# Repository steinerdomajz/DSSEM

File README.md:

# System for Environmental Monitoring in Protected Areas
**Master's Thesis Project** | Brno University of Technology (FEKT VUT)

This repository contains a demonstration of my final thesis project: an autonomous IoT system designed for long-term monitoring of acoustic and light pollution in sensitive environments.

Presentation available: DSSEM_presentation.pdf

**Key Features**:
- **Autonomous Operation**: Powered by a solar energy harvesting system.
- **Low-Power Design**: Optimized for long-term deployment in remote areas with minimal maintenance.
- **Connectivity**: Real-time data transmission via NB-IoT.
- **Sensor Precision**: Integrated high-sensitivity sensors for measuring environmental noise and light levels.

**Tech Stack**:
- **Electronics**: Custom PCB designed in KiCad.
- **Firmware**: Developed for MCU to handle sensor data and communication protocols.
- **Mechanical Design**: Protective environmental casing designed in SolidWorks.

--- **Hardware Design & Implementation:** ---

--- **Firmware:** ---

--- **Mechanical Design:** ---

--- **Implementation:** ---

Node-RED Flowchart:

InfluxDB Visualisation:

User Configuration Site (Web Serial API):

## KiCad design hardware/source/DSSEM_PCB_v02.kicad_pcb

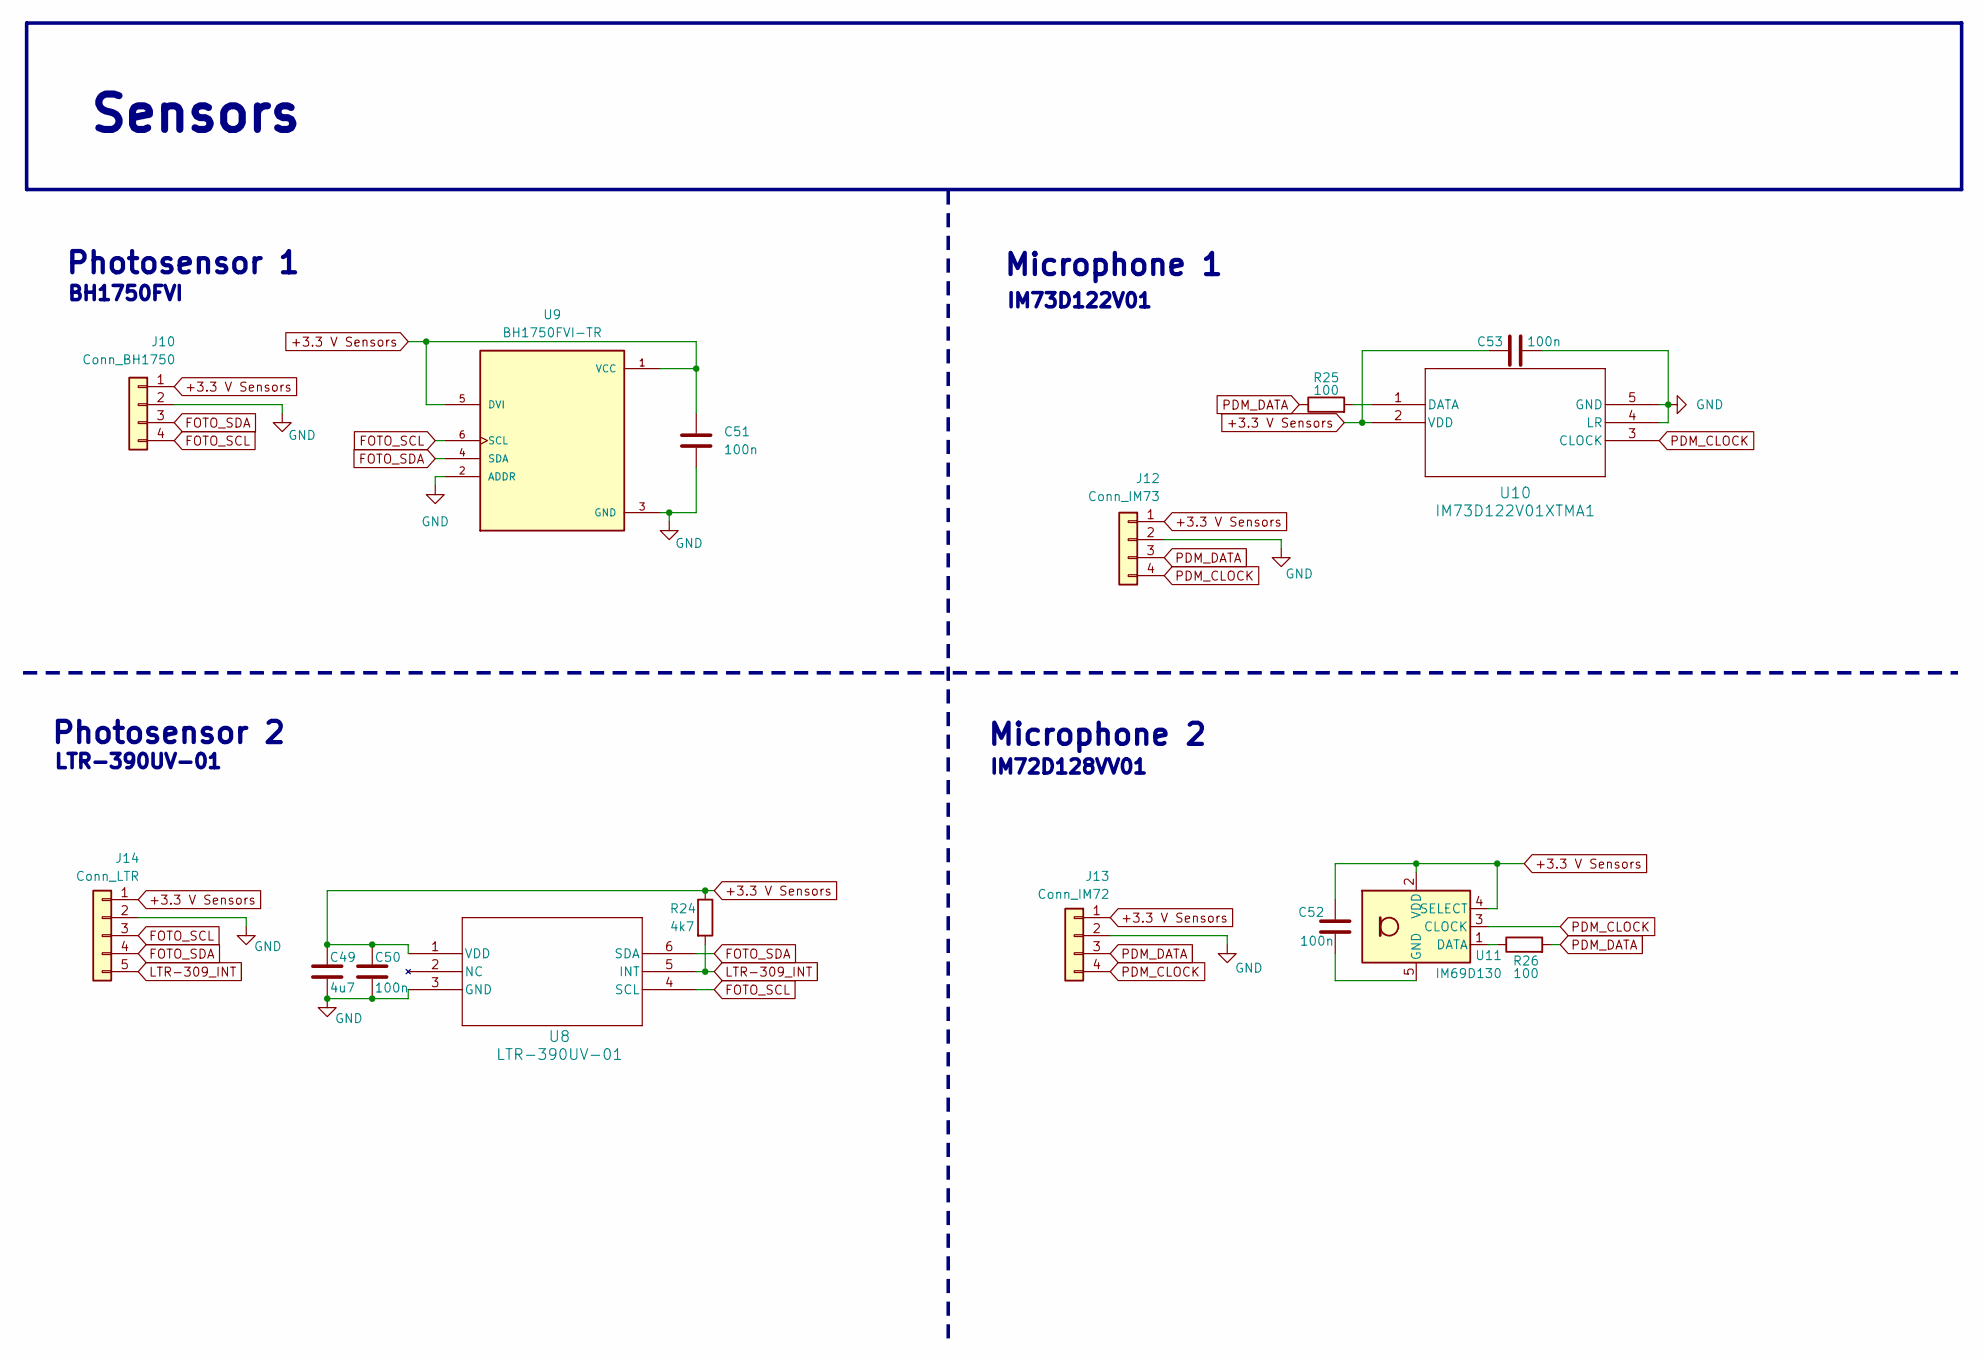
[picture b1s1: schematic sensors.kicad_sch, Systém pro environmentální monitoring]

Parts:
C49: 4u7; C_0603_1608Metric_Pad1.08x0.95mm_HandSolder
C50, C51, C52, C53: 100n; C_0603_1608Metric_Pad1.08x0.95mm_HandSolder
J10: Conn_BH1750; JST_GH_SM04B-GHS-TB_1x04-1MP_P1.25mm_Horizontal
J12: Conn_IM73; JST_GH_SM04B-GHS-TB_1x04-1MP_P1.25mm_Horizontal
J13: Conn_IM72; JST_GH_SM04B-GHS-TB_1x04-1MP_P1.25mm_Horizontal
J14: Conn_LTR; JST_GH_SM05B-GHS-TB_1x05-1MP_P1.25mm_Horizontal
R24: 4k7; R_0603_1608Metric_Pad0.98x0.95mm_HandSolder
R25, R26: 100; R_0603_1608Metric_Pad0.98x0.95mm_HandSolder
U8: LTR-390UV-01; SMD6_LTR-390UV-01_LTO
U9: BH1750FVI-TR; XDCR_BH1750FVI-TR; PARTREV D
U10: IM73D122V01XTMA1; Infineon_PG-LLGA-5-2
U11: IM69D130; Infineon_PG-LLGA-5-1

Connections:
+3.3 V Sensors: C49.1, C50.1, C51.1, C52.1, C53.1, J10.1, J12.1, J13.1, J14.1, R24.1, U8.1 (VDD), U9.1 (VCC), U9.5 (DVI), U10.2 (VDD), U11.2 (VDD), U11.4 (SELECT); also elsewhere on the board
FOTO_SCL: J10.4, J14.3, U8.4 (SCL), U9.6 (SCL); also elsewhere on the board
FOTO_SDA: J10.3, J14.4, U8.6 (SDA), U9.4 (SDA); also elsewhere on the board
GND: C49.2, C50.2, C51.2, C53.2, J10.2, J12.2, J13.2, J14.2, U8.3 (GND), U9.2 (ADDR), U9.3 (GND), U10.4 (LR), U10.5 (GND); also elsewhere on the board
LTR-309_INT: J14.5, R24.2, U8.5 (INT); also elsewhere on the board
unnamed: R25.2, U10.1 (DATA)
unnamed: R26.1, U11.1 (DATA)
unnamed: C52.2, U11.5 (GND)
PDM_CLOCK: J12.4, J13.4, U10.3 (CLOCK), U11.3 (CLOCK); also elsewhere on the board
PDM_DATA: J12.3, J13.3, R25.1, R26.2; also elsewhere on the board

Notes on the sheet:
Microphone 2
BH1750FVI
Photosensor 1
LTR-390UV-01
IM73D122V01
IM72D128VV01
Photosensor 2
Sensors
Microphone 1

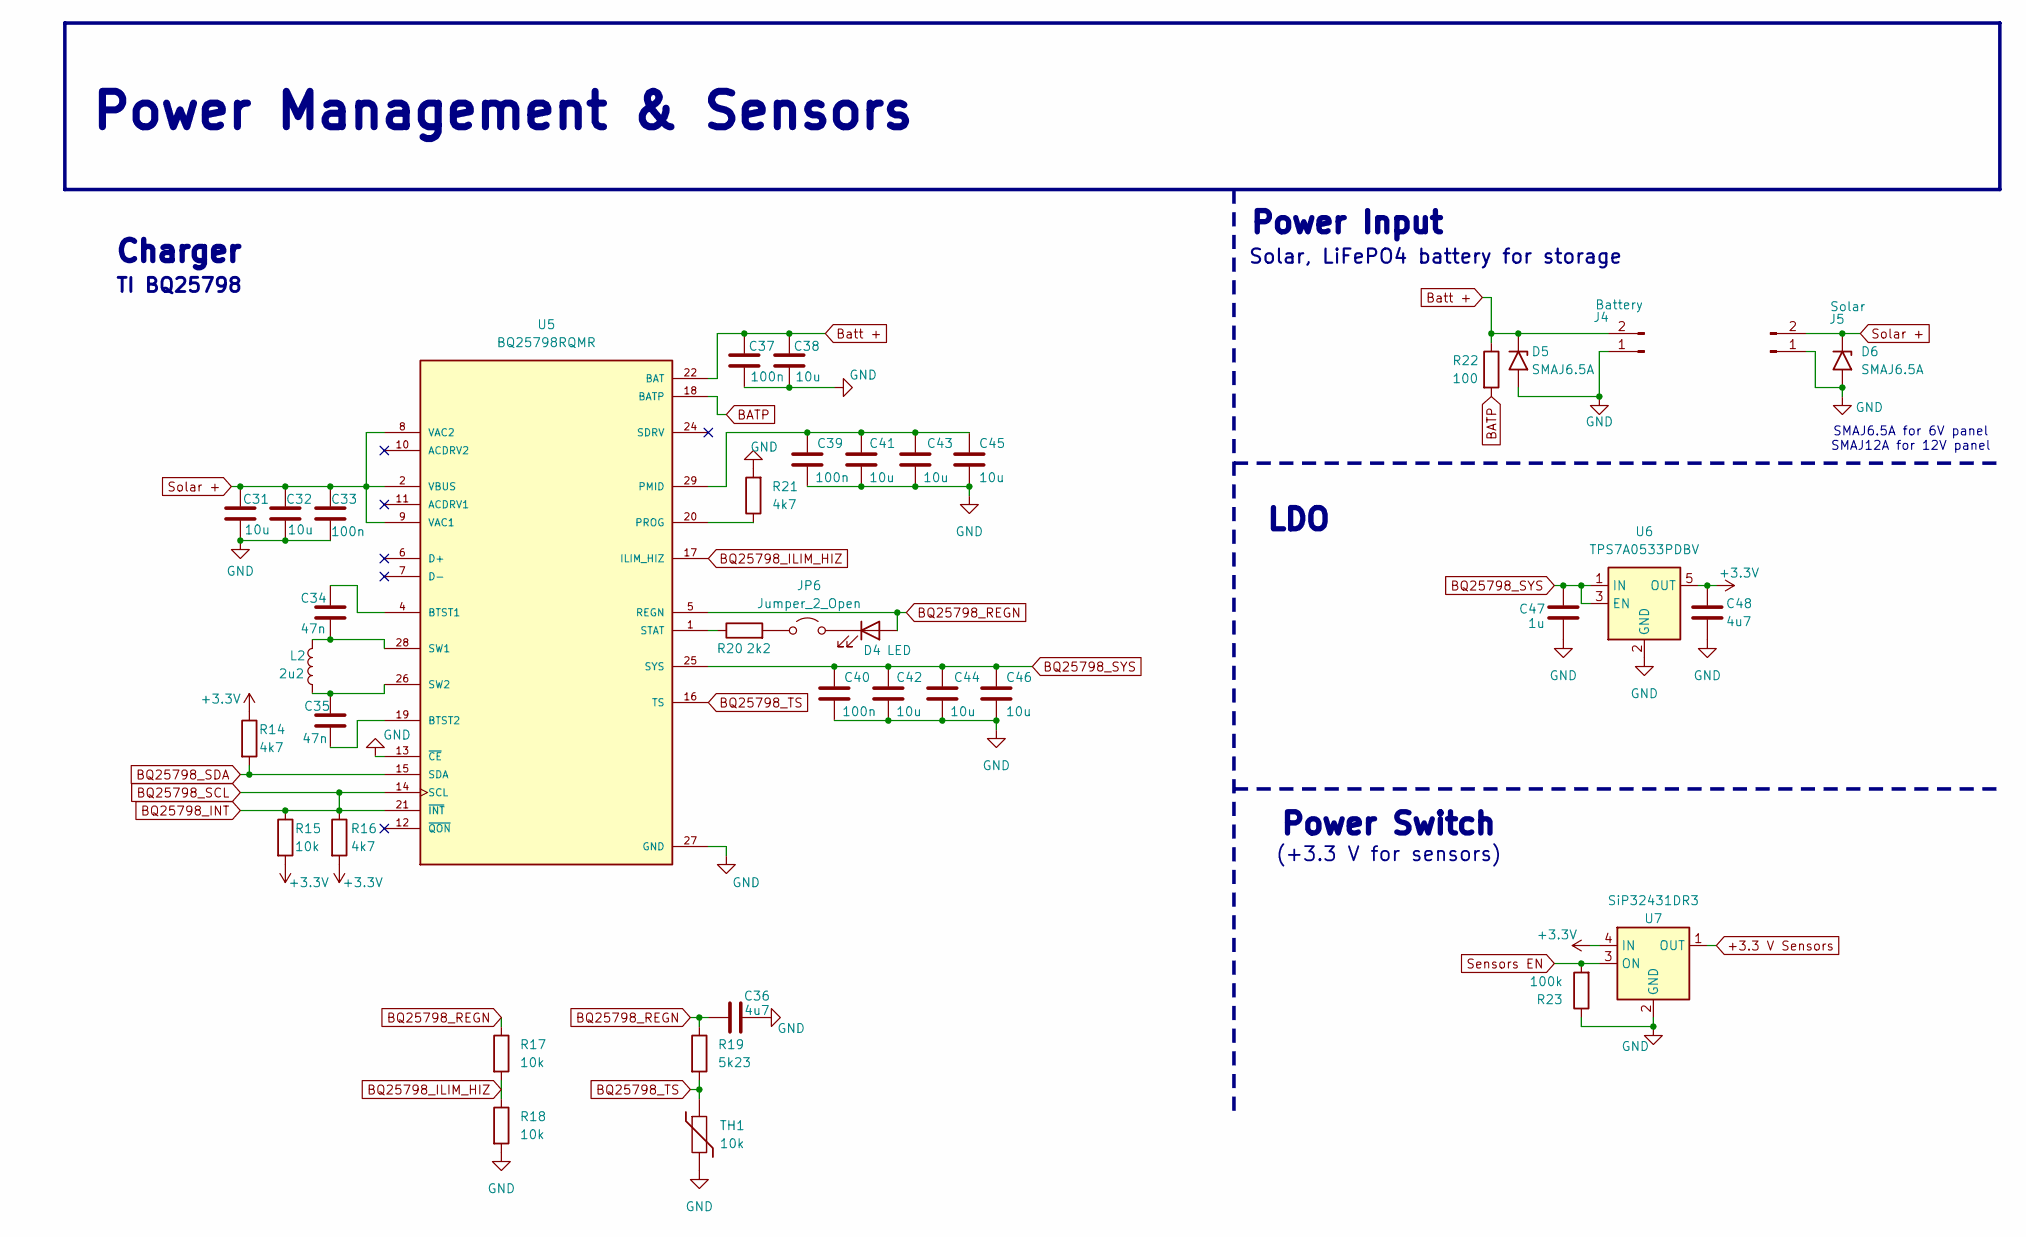
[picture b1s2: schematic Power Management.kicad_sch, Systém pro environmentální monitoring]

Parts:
C31, C32, C38, C41, C42, C43, C44, C45, C46: 10u; C_0603_1608Metric_Pad1.08x0.95mm_HandSolder
C33, C37, C39, C40: 100n; C_0603_1608Metric_Pad1.08x0.95mm_HandSolder
C34, C35: 47n; C_0603_1608Metric_Pad1.08x0.95mm_HandSolder
C36, C48: 4u7; C_0603_1608Metric_Pad1.08x0.95mm_HandSolder
C47: 1u; C_0603_1608Metric_Pad1.08x0.95mm_HandSolder
D4: LED; LED_0603_1608Metric
D5, D6: SMAJ6.5A; D_SMA
J4: Battery; TerminalBlock_Phoenix_MKDS-1,5-2-5.08_1x02_P5.08mm_Horizont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
J5: Solar; TerminalBlock_Phoenix_MKDS-1,5-2-5.08_1x02_P5.08mm_Horizont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
JP6: Jumper_2_Open; PinHeader_1x02_P1.27mm_Vertical
L2: 2u2; L_Bourns-SRN4018
R14, R16, R21: 4k7; R_0603_1608Metric_Pad0.98x0.95mm_HandSolder
R15, R17, R18: 10k; R_0603_1608Metric_Pad0.98x0.95mm_HandSolder
R19: 5k23; R_0603_1608Metric_Pad0.98x0.95mm_HandSolder
R20: 2k2; R_0603_1608Metric_Pad0.98x0.95mm_HandSolder
R22: 100; R_0603_1608Metric_Pad0.98x0.95mm_HandSolder
R23: 100k; R_0603_1608Metric_Pad0.98x0.95mm_HandSolder
TH1: 10k; R_0603_1608Metric_Pad0.98x0.95mm_HandSolder
U5: BQ25798RQMR; IC_BQ25798RQMR; PARTREV B
U6: TPS7A0533PDBV; SOT-23-5
U7: SiP32431DR3; SOT-363_SC-70-6

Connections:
+3.3 V Sensors: U7.1 (OUT); also elsewhere on the board
+3.3V: C48.1, R14.1, R15.2, R16.2, U6.5 (OUT), U7.4 (IN); also elsewhere on the board
BATP: R22.2, U5.18 (BATP)
BQ25798_ILIM_HIZ: R17.2, R18.1, U5.17 (ILIM_HIZ)
BQ25798_INT: R15.1, R16.1, U5.14 (SCL), U5.21 (~INT); also elsewhere on the board
BQ25798_REGN: C36.1, D4.2 (A), R17.1, R19.1, U5.5 (REGN)
BQ25798_SDA: R14.2, U5.15 (SDA); also elsewhere on the board
BQ25798_SYS: C40.1, C42.1, C44.1, C46.1, C47.1, U5.25 (SYS), U6.1 (IN), U6.3 (EN); also elsewhere on the board
BQ25798_TS: R19.2, TH1.1, U5.16 (TS)
Batt +: C37.1, C38.1, D5.1 (A1), J4.2, R22.1, U5.22 (BAT), U5.23 (BAT)
GND: C31.2, C32.2, C33.2, C36.2, C37.2, C38.2, C39.2, C40.2, C41.2, C42.2, C43.2, C44.2, C45.2, C46.2, C47.2, C48.2, D5.2 (A2), D6.2 (A2), J4.1, J5.1, R18.2, R21.2, R23.1, TH1.2, U5.13 (~CE), U5.27 (GND), U6.2 (GND), U7.2 (GND), U7.5 (GND); also elsewhere on the board
unnamed: D4.1 (K), JP6.2 (B)
unnamed: JP6.1 (A), R20.2
unnamed: C34.1, U5.4 (BTST1)
unnamed: C35.2, U5.19 (BTST2)
unnamed: C39.1, C41.1, C43.1, C45.1, U5.29 (PMID)
unnamed: R21.1, U5.20 (PROG)
unnamed: R20.1, U5.1 (STAT)
unnamed: C34.2, L2.2, U5.28 (SW1)
unnamed: C35.1, L2.1, U5.26 (SW2)
Sensors EN: R23.2, U7.3 (ON); also elsewhere on the board
Solar +: C31.1, C32.1, C33.1, D6.1 (A1), J5.2, U5.2 (VBUS), U5.3 (VBUS), U5.8 (VAC2), U5.9 (VAC1)

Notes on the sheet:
LDO
TI BQ25798
Solar, LiFePO4 battery for storage
(+3.3 V for sensors)
Power Management & Sensors
Power Input
Power Switch
Charger
SMAJ6.5A for 6V panel SMAJ12A for 12V panel

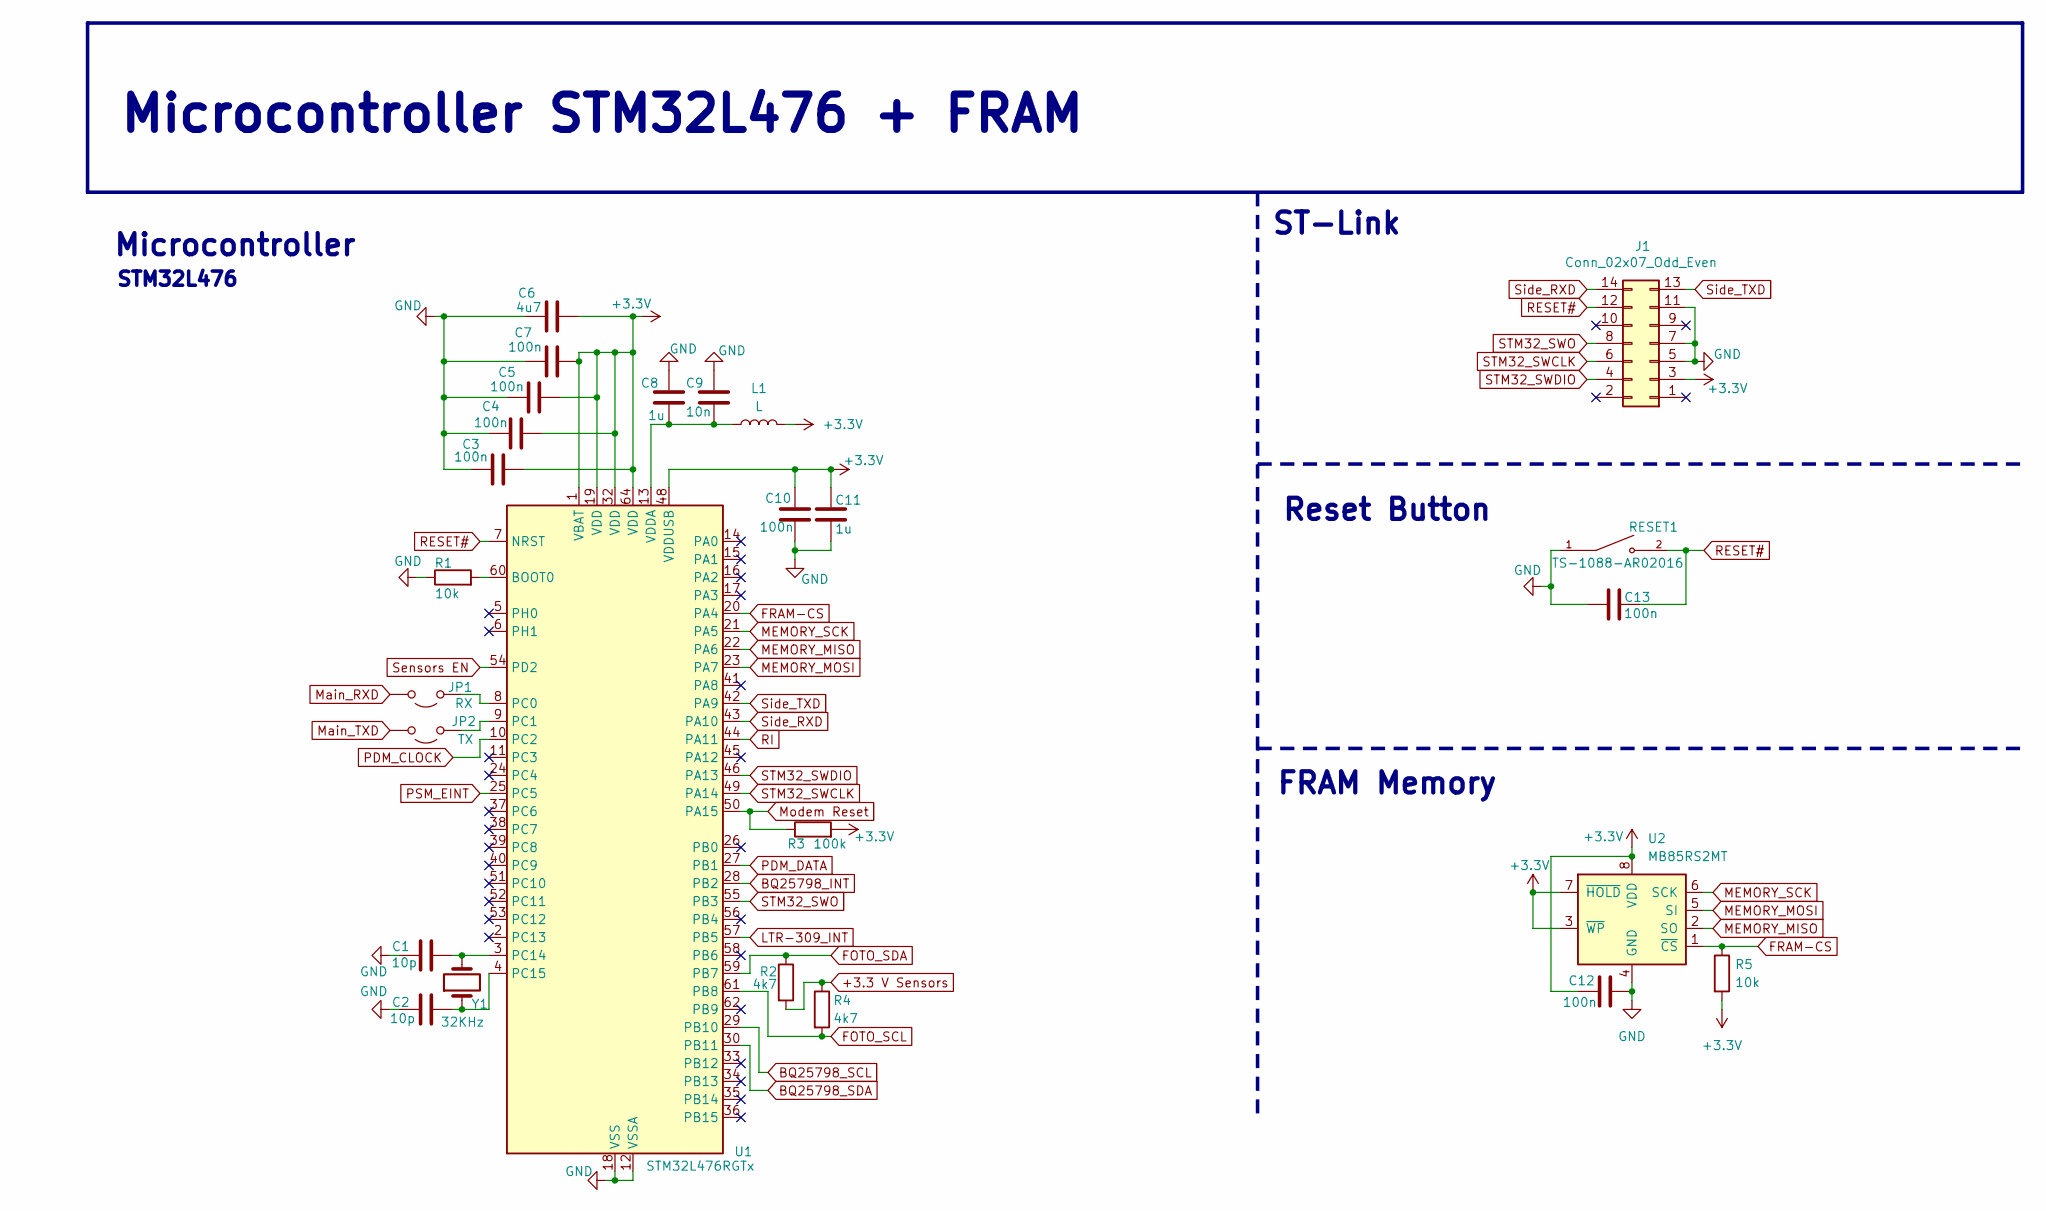
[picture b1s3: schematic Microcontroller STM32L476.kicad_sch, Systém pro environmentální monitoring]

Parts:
C1, C2: 10p; C_0603_1608Metric_Pad1.08x0.95mm_HandSolder
C3, C4, C5, C7, C10, C12, C13: 100n; C_0603_1608Metric_Pad1.08x0.95mm_HandSolder
C6: 4u7; C_0603_1608Metric_Pad1.08x0.95mm_HandSolder
C8, C11: 1u; C_0603_1608Metric_Pad1.08x0.95mm_HandSolder
C9: 10n; C_0603_1608Metric_Pad1.08x0.95mm_HandSolder
J1: Conn_02x07_Odd_Even; PinHeader_2x07_P1.27mm_Vertical
JP1: RX; PinHeader_1x02_P1.27mm_Vertical; LCSC C225477
JP2: TX; PinHeader_1x02_P1.27mm_Vertical; LCSC C225477
L1: L; L_0603_1608Metric_Pad1.05x0.95mm_HandSolder
R1, R5: 10k; R_0603_1608Metric_Pad0.98x0.95mm_HandSolder
R2, R4: 4k7; R_0603_1608Metric_Pad0.98x0.95mm_HandSolder
R3: 100k; R_0603_1608Metric_Pad0.98x0.95mm_HandSolder
RESET1: TS-1088-AR02016; SW_SPST_TS-1088-xR020; PARTREV N/A; LCSC C720477
U1: STM32L476RGTx; LQFP-64_10x10mm_P0.5mm
U2: MB85RS2MT; SOIC-8_3.9x4.9mm_P1.27mm
Y1: 32KHz; Crystal_SMD_3215-2Pin_3.2x1.5mm

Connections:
+3.3 V Sensors: R2.2, R4.1; also elsewhere on the board
+3.3V: C3.2, C4.2, C5.2, C6.2, C7.2, C10.1, C11.1, C12.1, J1.3, L1.2, R3.2, R5.2, U1.1 (VBAT), U1.19 (VDD), U1.32 (VDD), U1.48 (VDDUSB), U1.64 (VDD), U2.3 (~WP), U2.7 (~HOLD), U2.8 (VDD); also elsewhere on the board
BQ25798_INT: U1.28 (PB2), U1.29 (PB10); also elsewhere on the board
BQ25798_SDA: U1.30 (PB11); also elsewhere on the board
FOTO_SCL: R4.2, U1.61 (PB8); also elsewhere on the board
FOTO_SDA: R2.1, U1.59 (PB7); also elsewhere on the board
FRAM-CS: R5.1, U1.20 (PA4), U2.1 (~CS)
GND: C1.1, C2.1, C3.1, C4.1, C5.1, C6.1, C7.1, C8.1, C9.1, C10.2, C11.2, C12.2, C13.1, J1.5, J1.7, J1.11, R1.1, RESET1.1, U1.12 (VSSA), U1.18 (VSS), U1.31 (VSS), U1.47 (VSS), U1.63 (VSS), U2.4 (GND); also elsewhere on the board
LTR-309_INT: U1.57 (PB5); also elsewhere on the board
MEMORY_MISO: U1.22 (PA6), U2.2 (SO)
MEMORY_MOSI: U1.23 (PA7), U2.5 (SI)
MEMORY_SCK: U1.21 (PA5), U2.6 (SCK)
Main_RXD: JP1.2 (B); also elsewhere on the board
Main_TXD: JP2.2 (B); also elsewhere on the board
Modem Reset: R3.1, U1.50 (PA15); also elsewhere on the board
unnamed: JP1.1 (A), U1.8 (PC0)
unnamed: JP2.1 (A), U1.9 (PC1)
unnamed: R1.2, U1.60 (BOOT0)
unnamed: C1.2, U1.3 (PC14), Y1.2
unnamed: C2.2, U1.4 (PC15), Y1.1
unnamed: C8.2, C9.2, L1.1, U1.13 (VDDA)
PDM_CLOCK: U1.10 (PC2); also elsewhere on the board
PDM_DATA: U1.27 (PB1); also elsewhere on the board
PSM_EINT: U1.25 (PC5); also elsewhere on the board
RESET#: C13.2, J1.12, RESET1.2, U1.7 (NRST)
RI: U1.44 (PA11); also elsewhere on the board
STM32_SWCLK: J1.6, U1.49 (PA14)
STM32_SWDIO: J1.4, U1.46 (PA13)
STM32_SWO: J1.8, U1.55 (PB3)
Sensors EN: U1.54 (PD2); also elsewhere on the board
Side_RXD: J1.14, U1.43 (PA10)
Side_TXD: J1.13, U1.42 (PA9)

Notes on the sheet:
Microcontroller
STM32L476
ST-Link
Reset Button
FRAM Memory
Microcontroller STM32L476 + FRAM

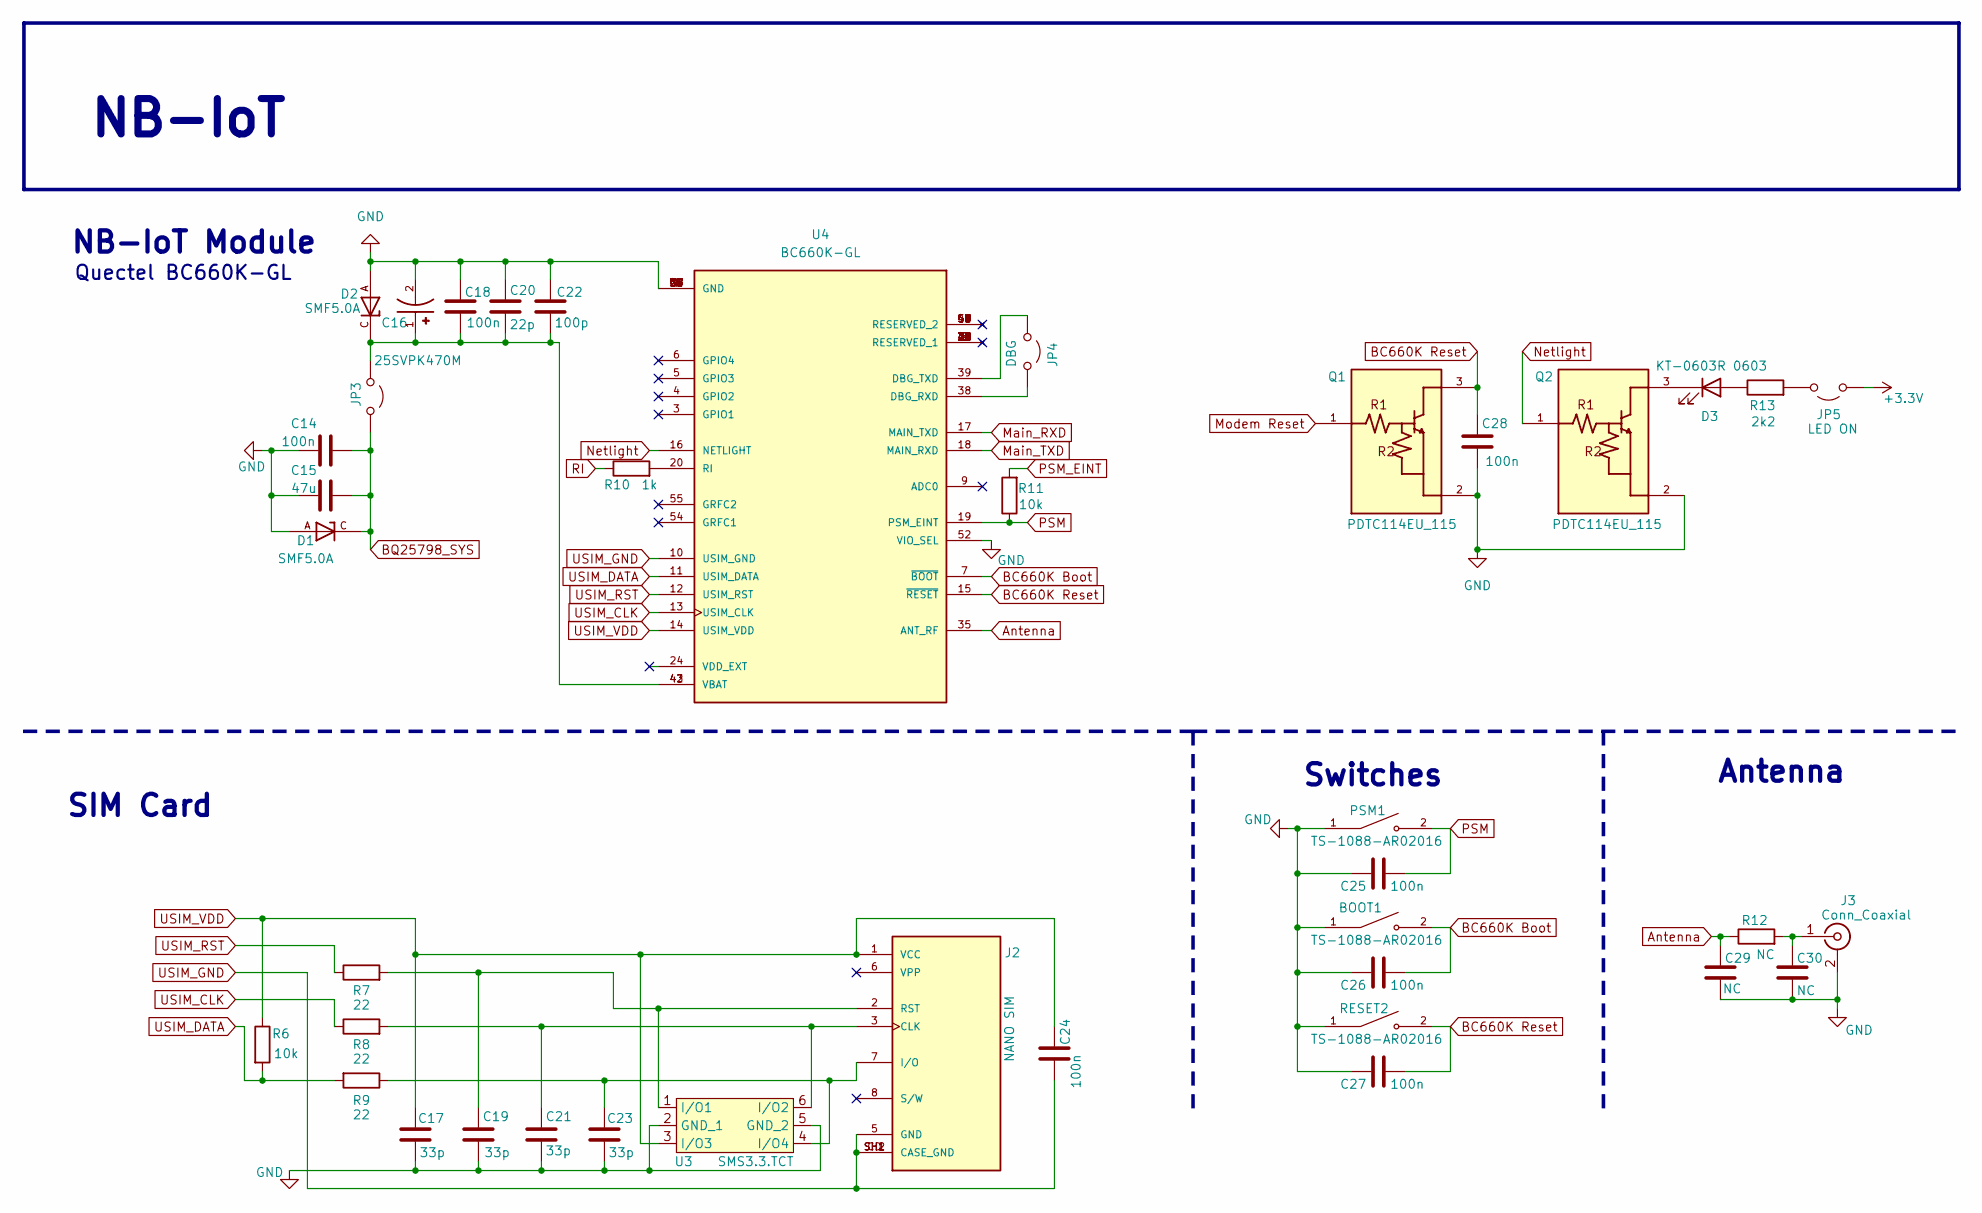
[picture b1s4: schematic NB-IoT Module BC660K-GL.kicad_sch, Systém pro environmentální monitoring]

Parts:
BOOT1: TS-1088-AR02016; SW_TS-1088-AR02016; PARTREV N/A
C14, C18: 100n; C_0603_1608Metric_Pad1.08x0.95mm_HandSolder
C15: 47u; C_0805_2012Metric_Pad1.18x1.45mm_HandSolder
C16: 25SVPK470M; CAP_25SVPK470M; PARTREV 28-Jun-19; LCSC C454276
C17, C19, C21, C23: 33p; C_0603_1608Metric_Pad1.08x0.95mm_HandSolder; LCSC C1663
C20: 22p; C_0603_1608Metric_Pad1.08x0.95mm_HandSolder
C22: 100p; C_0603_1608Metric_Pad1.08x0.95mm_HandSolder
C24, C25, C26, C27, C28: 100n; C_0603_1608Metric_Pad1.08x0.95mm_HandSolder; LCSC C14663
C29, C30: NC; C_0603_1608Metric_Pad1.08x0.95mm_HandSolder
D1, D2: SMF5.0A; SODFL3718X102N; PARTREV D2103
D3: KT-0603R 0603; LED_0603_1608Metric; LCSC C2286
J2: NANO SIM; nanoSIM_Hinged_CUI_NSIM-2-C; PARTREV 1.0; LCSC C77877
J3: Conn_Coaxial; U.FL_Molex_MCRF_73412-0110_Vertical
JP3: +3.3V; PinHeader_1x02_P2.54mm_Vertical; LCSC C225477
JP4: DBG; PinHeader_1x02_P2.54mm_Vertical; LCSC C225477
JP5: LED ON; PinHeader_1x02_P1.27mm_Vertical; LCSC C706997
PSM1: TS-1088-AR02016; SW_TS-1088-AR02016; PARTREV N/A
Q1, Q2: PDTC114EU_115; SOT65P210X110-3N; PARTREV 12; LCSC C135830
R6, R11: 10k; R_0603_1608Metric_Pad0.98x0.95mm_HandSolder
R7, R8, R9: 22; R_0603_1608Metric_Pad0.98x0.95mm_HandSolder; LCSC C23345
R10: 1k; R_0603_1608Metric_Pad0.98x0.95mm_HandSolder
R12: NC; R_0603_1608Metric_Pad0.98x0.95mm_HandSolder
R13: 2k2; R_0603_1608Metric_Pad0.98x0.95mm_HandSolder; LCSC C4190
RESET2: TS-1088-AR02016; SW_TS-1088-AR02016; PARTREV N/A
U3: SMS3.3.TCT; SOT-23-6; LCSC C780132
U4: BC660K-GL; XCVR_BC660K-GL; PARTREV 1.2

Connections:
+3.3V: JP5.1 (A); also elsewhere on the board
Antenna: C29.1, R12.1, U4.35 (ANT_RF)
BC660K Boot: BOOT1.2, C26.1, U4.7 (~BOOT)
BC660K Reset: C27.1, C28.1, Q1.3, RESET2.2, U4.15 (~RESET)
BQ25798_SYS: C14.2, C15.2, D1.C, JP3.2 (B); also elsewhere on the board
GND: BOOT1.1, C14.1, C15.1, C16.2, C17.1, C18.1, C19.2, C20.1, C21.1, C22.1, C23.2, C25.2, C26.2, C27.2, C28.2, C29.2, C30.2, D1.A, D2.A, J3.2 (Ext), PSM1.1, Q1.2, Q2.2, RESET2.1, U3.2 (GND_1), U3.5 (GND_2), U4.1 (GND), U4.27 (GND), U4.34 (GND), U4.36 (GND), U4.37 (GND), U4.40 (GND), U4.41 (GND), U4.52 (VIO_SEL), U4.56 (GND), U4.57 (GND), U4.58 (GND); also elsewhere on the board
Main_RXD: U4.17 (MAIN_TXD); also elsewhere on the board
Main_TXD: U4.18 (MAIN_RXD); also elsewhere on the board
Modem Reset: Q1.1; also elsewhere on the board
unnamed: D3.2 (A), R13.1
unnamed: D3.1 (K), Q2.3
unnamed: C21.2, J2.3 (CLK), R8.2, U3.6 (I/O2)
unnamed: C23.1, J2.7 (I/O), R9.1, U3.4 (I/O4)
unnamed: C19.1, J2.2 (RST), R7.2, U3.1 (I/O1)
unnamed: C30.1, J3.1 (In), R12.2
unnamed: C16.1, C18.2, C20.2, C22.2, D2.C, JP3.1 (A), U4.42 (VBAT), U4.43 (VBAT)
unnamed: JP4.1 (A), U4.39 (DBG_TXD)
unnamed: JP4.2 (B), U4.38 (DBG_RXD)
unnamed: JP5.2 (B), R13.2
unnamed: R10.2, U4.20 (RI)
Netlight: Q2.1, U4.16 (NETLIGHT)
PSM: C25.1, PSM1.2, R11.1, U4.19 (PSM_EINT)
PSM_EINT: R11.2; also elsewhere on the board
RI: R10.1; also elsewhere on the board
USIM_CLK: R8.1, U4.13 (USIM_CLK)
USIM_DATA: R6.2, R9.2, U4.11 (USIM_DATA)
USIM_GND: C24.2, J2.5 (GND), J2.CD (CASE_GND), J2.SH1 (CASE_GND), J2.SH2 (CASE_GND), U4.10 (USIM_GND)
USIM_RST: R7.1, U4.12 (USIM_RST)
USIM_VDD: C17.2, C24.1, J2.1 (VCC), R6.1, U3.3 (I/O3), U4.14 (USIM_VDD)

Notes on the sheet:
NB-IoT Module
SIM Card
Quectel BC660K-GL
NB-IoT
Antenna
Switches

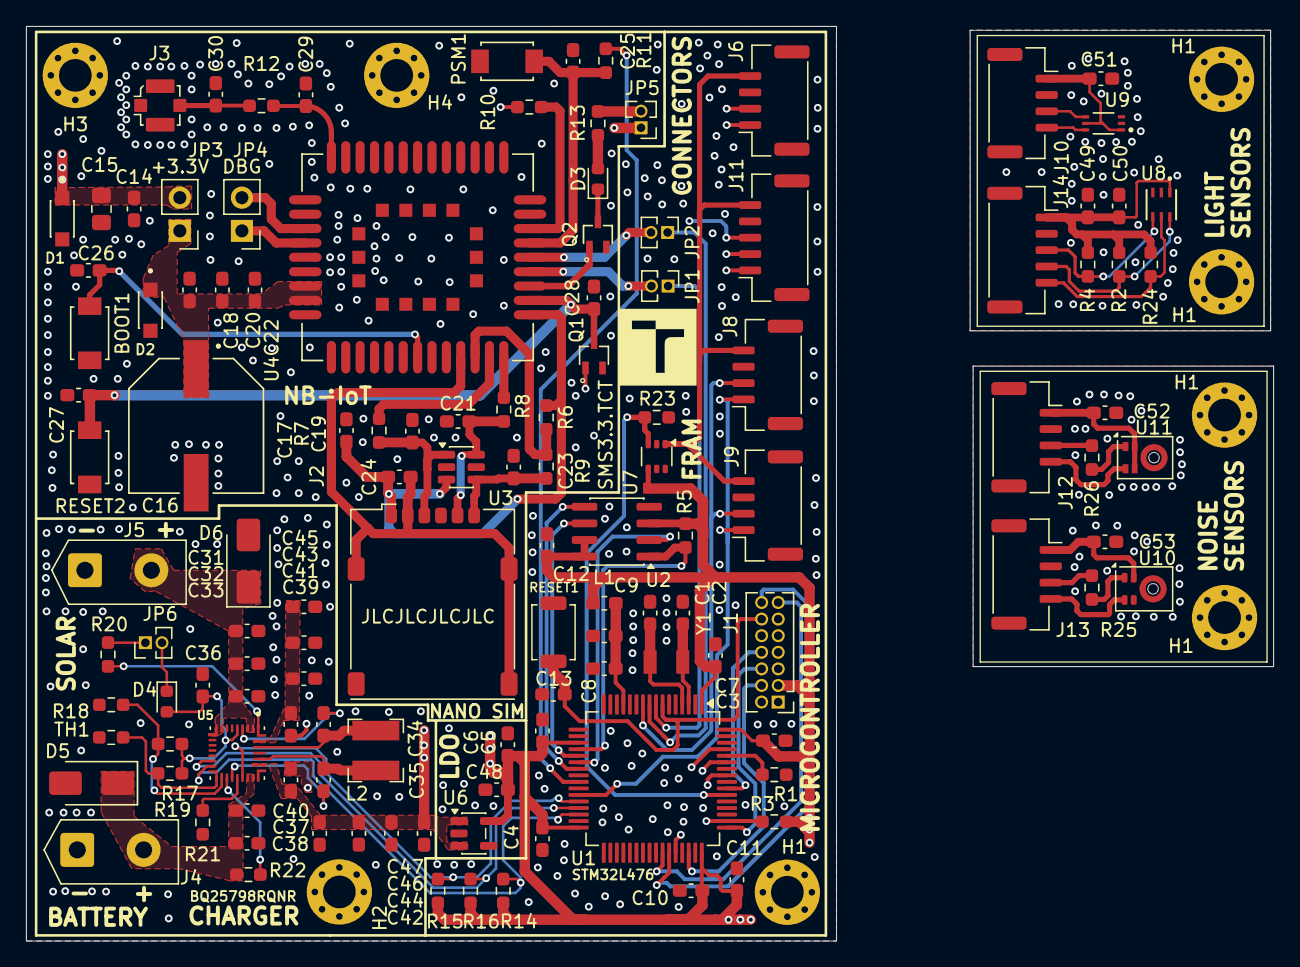
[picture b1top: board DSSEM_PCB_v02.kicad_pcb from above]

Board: 4 copper layers, 95.5 x 70.0 mm, 133 parts (0 on the bottom side), 72 nets.

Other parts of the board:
H1, H1#2, H1#3, H1#4, H1#5, H2, H3, H4: MountingHole_2.5mm_Pad_Via
J6: Conn_BH1750; JST_GH_SM04B-GHS-TB_1x04-1MP_P1.25mm_Horizontal
J8: Conn_IM73; JST_GH_SM04B-GHS-TB_1x04-1MP_P1.25mm_Horizontal
J9: Conn_IM72; JST_GH_SM04B-GHS-TB_1x04-1MP_P1.25mm_Horizontal
J11: Conn_LTR; JST_GH_SM05B-GHS-TB_1x05-1MP_P1.25mm_Horizontal

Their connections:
+3.3 V Sensors: J6.4, J8.4, J9.4, J11.5; also elsewhere on the board
FOTO_SCL: J6.2, J11.3; also elsewhere on the board
FOTO_SDA: J6.1, J11.2; also elsewhere on the board
GND: H1#5.1, H2.1, H3.1, H4.1, J6.3, J8.3, J9.3, J11.4; also elsewhere on the board
LTR-309_INT: J11.1; also elsewhere on the board
PDM_CLOCK: J8.2, J9.2; also elsewhere on the board
PDM_DATA: J8.1, J9.1; also elsewhere on the board

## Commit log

2026-04-06 /hardware update
2026-04-06 Create /hardware
2026-04-06 Source files for /hardware
2026-04-06 Create test
2026-04-06 Visualizations for /hardware
2026-05-05 DSSEM presentation
2026-05-05 Rename DSSEM.pdf to DSSEM_presentation.pdf
